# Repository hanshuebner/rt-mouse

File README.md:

# USB Mouse Adapter for IBM 6150 (RT PC)

This repository contains firmware for a Raspberry Pi Pico to act as
an adapter to make a USB mouse usable with the IBM 6150 (RT PC).

In addition to the Pi Pico, a MAX3232 and a couple of capacitors
are required to adapt the serial port of the Pico to RS232 levels.

Schematics are provided in the pcb/ directory.  I've not actually
designed a PCB as I believe that nobody would care, and my bread-
boarded prototype suffices for me.

The research/ directory contains information about the mouse
protocol, historic header files and mouse emulation implementations
that I used for testing before implementing the Pico firmware.

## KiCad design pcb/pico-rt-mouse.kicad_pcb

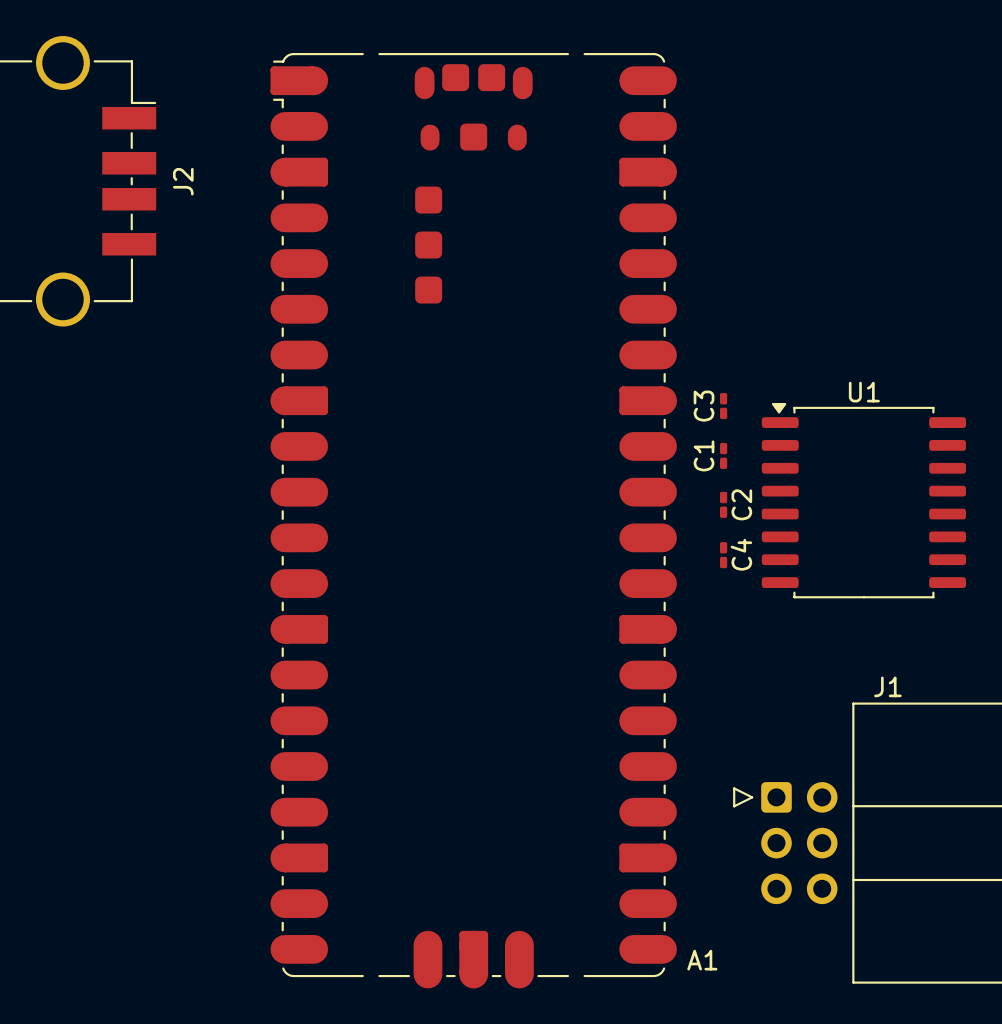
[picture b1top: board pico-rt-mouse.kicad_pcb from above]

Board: 2 copper layers, 8 parts (0 on the bottom side), 15 nets, no tracks yet.

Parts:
A1: RaspberryPi_Pico; RaspberryPi_Pico_SMD
C1, C2, C3, C4: 100n; C_0201_0603Metric_Pad0.64x0.40mm_HandSolder
J1: RT MOUSE; IDC-Header_2x03_P2.54mm_Horizontal
J2: USB_A; USB_A_TE_292303-7_Horizontal
U1: MAX3232; SOIC-16W_7.5x10.3mm_P1.27mm

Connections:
+3.3V: A1.36 (3V3), U1.16 (VCC)
+5V: A1.39 (VSYS), J1.5, J2.1 (VBUS)
GND: A1.3 (GND), A1.8 (GND), A1.13 (GND), A1.18 (GND), A1.23 (GND), A1.28 (GND), A1.38 (GND), A1.D2 (GND), A1.TP1 (USB_GND), C3.2, C4.2, J1.1, J2.4 (GND), J2.5 (Shield), U1.8 (R2IN), U1.10 (T2IN), U1.15 (GND)
unnamed: C1.1, U1.1 (C1+)
unnamed: C1.2, U1.3 (C1-)
unnamed: C2.1, U1.4 (C2+)
unnamed: C2.2, U1.5 (C2-)
unnamed: C3.1, U1.2 (VS+)
unnamed: C4.1, U1.6 (VS-)
RT_RX: J1.6, U1.14 (T1OUT)
RT_TX: J1.2, U1.13 (R1IN)
UART1_RX: A1.12 (GPIO9), U1.12 (R1OUT)
UART1_TX: A1.11 (GPIO8), U1.11 (T1IN)
USB_DM: A1.TP2 (USB_DM), J2.2 (D-)
USB_DP: A1.TP3 (USB_DP), J2.3 (D+)

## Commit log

2025-05-11 wiring info
2025-05-11 update js/README.md to be more accurate to the actual implementation
2025-05-11 swift/README.md updates
2025-05-12 compiles pico-rt-mouse, no functionality yet
2025-05-12 rt mouse protocol implementation and readme (untested)
2025-05-12 add schematics & pcb
2025-05-12 add openocd.cfg
2025-05-12 somewhat working, but only in one direction
2025-05-12 scale deltas correctly
2025-07-13 fixes to make it work
2025-07-13 Reorganize
